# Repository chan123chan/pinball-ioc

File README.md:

# pinball-ioc
Hard and Software for our pinball machine

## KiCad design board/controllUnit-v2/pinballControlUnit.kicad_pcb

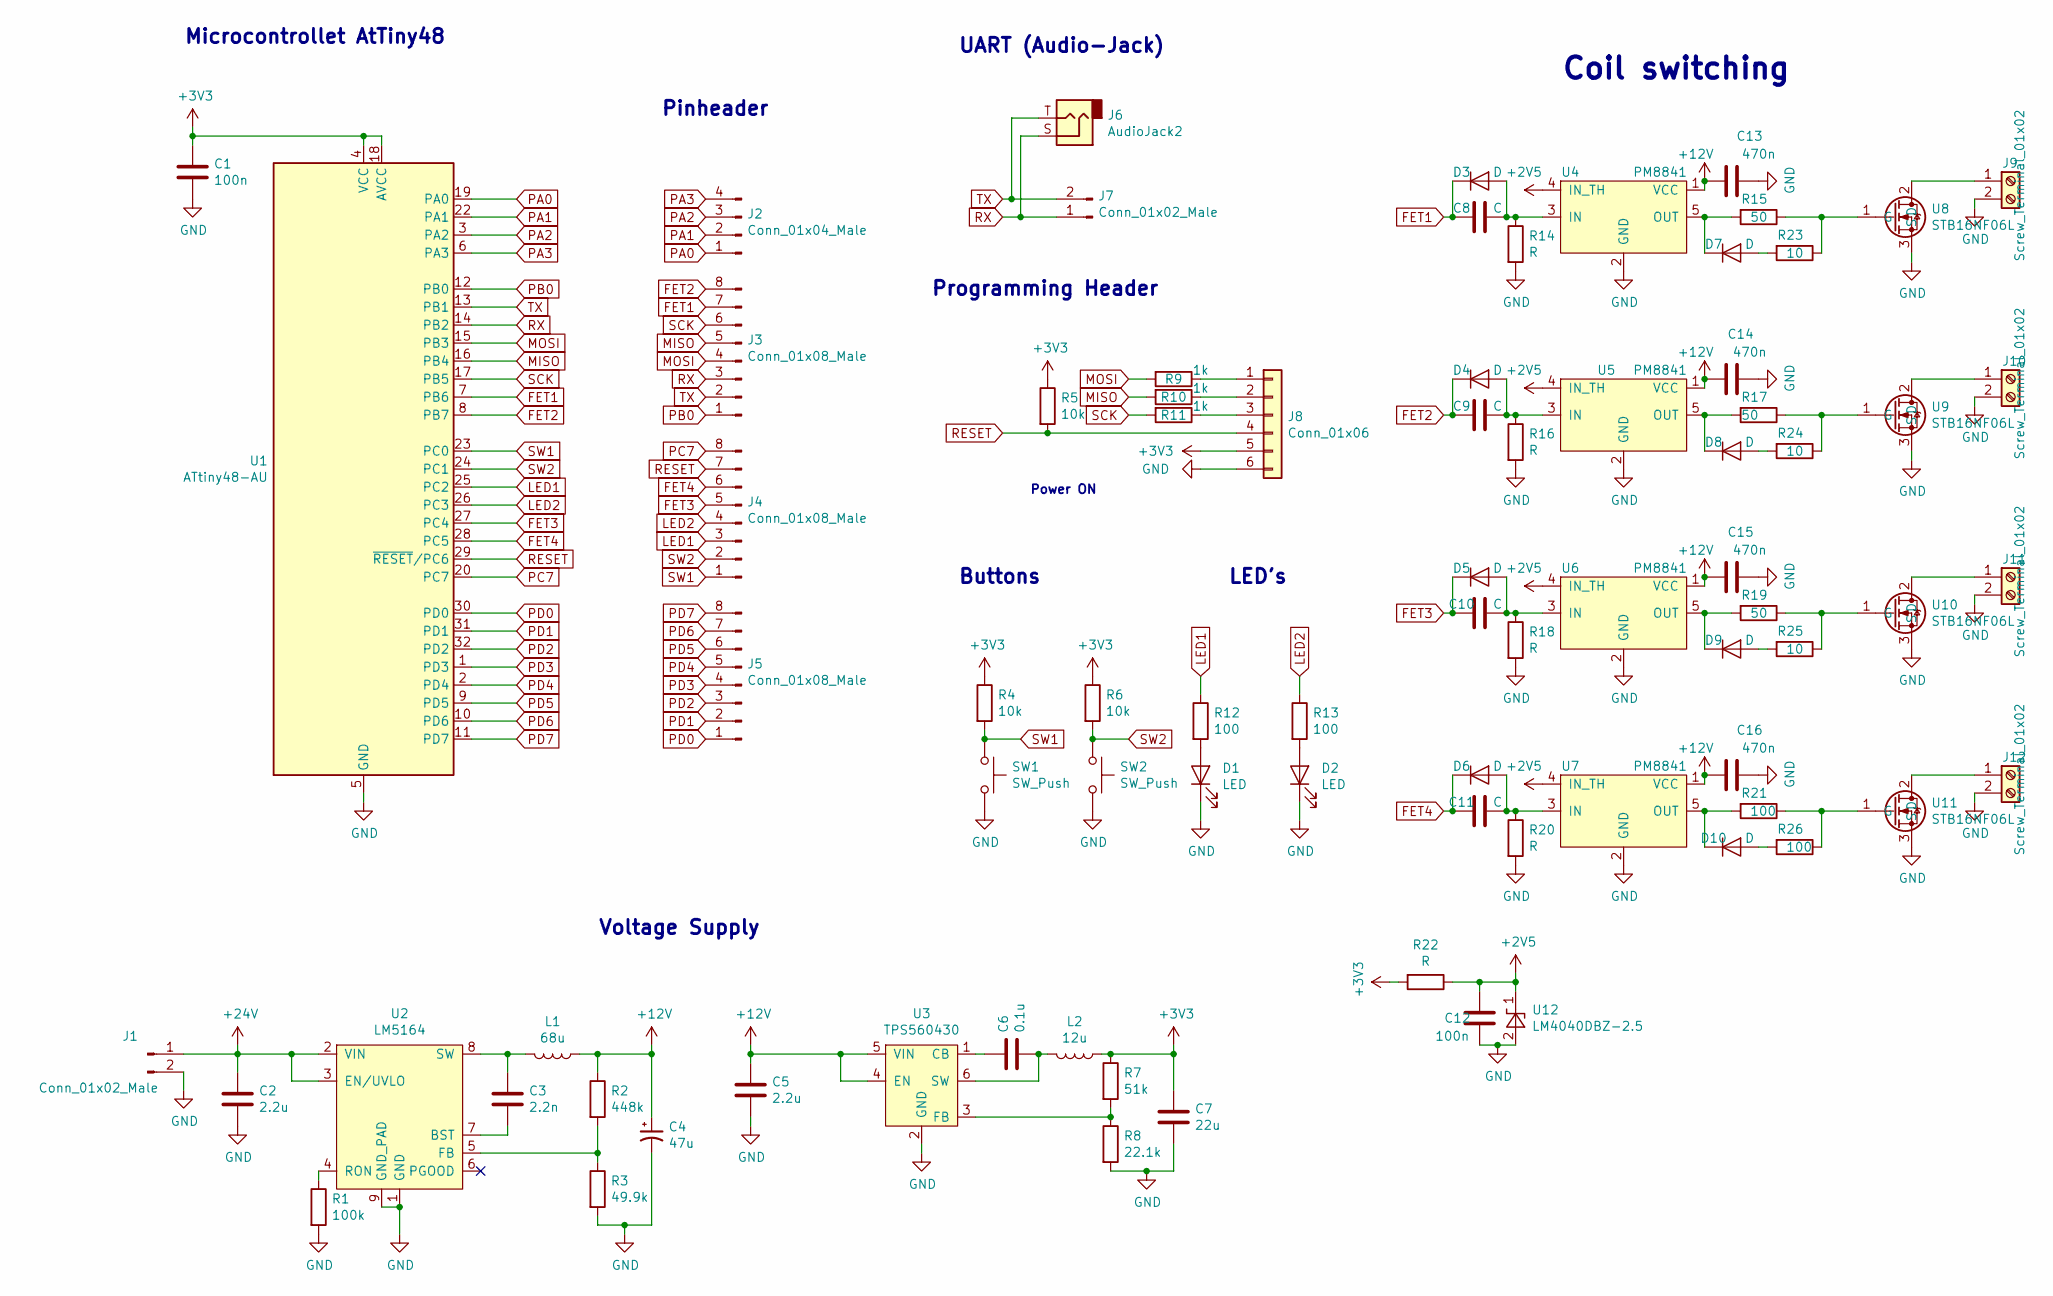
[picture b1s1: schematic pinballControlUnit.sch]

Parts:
C1, C12: 100n; C_0805_2012Metric
C2: 2.2u; C_1206_3216Metric
C3: 2.2n; C_0805_2012Metric
C4: 47u; C_Elec_6.3x5.8
C5: 2.2u; C_0805_2012Metric
C6: 0.1u; C_0805_2012Metric
C7: 22u; C_0805_2012Metric
C8, C9, C10, C11: C; C_0805_2012Metric
C13, C14, C15, C16: 470n; C_0805_2012Metric
D1, D2: LED; LED_0805_2012Metric
D3, D4, D5, D6, D7, D8, D9, D10: D; LED_0805_2012Metric
J1, J7: Conn_01x02_Male; PinHeader_1x02_P2.54mm_Vertical
J2: Conn_01x04_Male; PinHeader_1x04_P2.54mm_Vertical
J3, J4, J5: Conn_01x08_Male; PinHeader_1x08_P2.54mm_Vertical
J6: AudioJack2; Jack_3.5mm_CUI_SJ-3523-SMT_Horizontal
J8: Conn_01x06; PinHeader_1x06_P2.54mm_Vertical
J9, J10, J11, J12: Screw_Terminal_01x02; TerminalBlock_MetzConnect_Type011_RT05502HBWC_1x02_P5.00mm_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
L1: 68u; L_MSS1246-683MLB
L2: 12u; L_SDR0403-120ML
R1: 100k; R_0805_2012Metric
R2: 448k; R_0805_2012Metric
R3: 49.9k; R_0805_2012Metric
R4, R5, R6: 10k; R_0805_2012Metric
R7: 51k; R_0805_2012Metric
R8: 22.1k; R_0805_2012Metric
R9, R10, R11: 1k; R_0805_2012Metric
R12, R13, R21, R26: 100; R_0805_2012Metric
R14, R16, R18, R20, R22: R; R_0805_2012Metric
R15, R17, R19: 50; R_0805_2012Metric
R23, R24, R25: 10; R_0805_2012Metric
SW1, SW2: SW_Push; SW_SPST_B3S-1000
U1: ATtiny48-AU; TQFP-32_7x7mm_P0.8mm
U2: LM5164; TI_SO-PowerPAD-8
U3: TPS560430; SOT-23-6_Handsoldering
U4, U5, U6, U7: PM8841; SOT-23-5_HandSoldering
U8, U9, U10, U11: STB16NF06L; TO-263-2
U12: LM4040DBZ-2.5; SOT-23

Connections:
+2V5: C12.1, R22.1, U4.4 (IN_TH), U5.4 (IN_TH), U6.4 (IN_TH), U7.4 (IN_TH), U12.1 (K)
+3V3: C1.1, C7.1, J8.5, L2.1, R4.1, R5.1, R6.1, R7.1, R22.2, U1.4 (VCC), U1.18 (AVCC)
+12V: C4.1, C5.1, C13.1, C14.1, C15.1, C16.1, L1.1, R2.1, U3.4 (EN), U3.5 (VIN), U4.1 (VCC), U5.1 (VCC), U6.1 (VCC), U7.1 (VCC)
+24V: C2.1, J1.1, U2.2 (VIN), U2.3 (EN/UVLO)
FET1: C8.2, D3.1 (K), J3.7, U1.7 (PB6)
FET2: C9.2, D4.1 (K), J3.8, U1.8 (PB7)
FET3: C10.2, D5.1 (K), J4.5, U1.27 (PC4)
FET4: C11.2, D6.1 (K), J4.6, U1.28 (PC5)
GND: C1.2, C2.2, C4.2, C5.2, C7.2, C12.2, C13.2, C14.2, C15.2, C16.2, D1.1 (K), D2.1 (K), J1.2, J8.6, J9.2, J10.2, J11.2, J12.2, R1.2, R3.2, R8.2, R14.2, R16.2, R18.2, R20.2, SW1.2, SW2.2, U1.5 (GND), U1.21 (GND), U2.1 (GND), U2.9 (GND_PAD), U3.2 (GND), U4.2 (GND), U5.2 (GND), U6.2 (GND), U7.2 (GND), U8.3 (S), U9.3 (S), U10.3 (S), U11.3 (S), U12.2 (A)
LED1: J4.3, R12.1, U1.25 (PC2)
LED2: J4.4, R13.1, U1.26 (PC3)
MISO: J3.5, R10.2, U1.16 (PB4)
MOSI: J3.4, R9.2, U1.15 (PB3)
unnamed: C3.1, L1.2, U2.8 (SW)
unnamed: C3.2, U2.7 (BST)
unnamed: C6.1, U3.1 (CB)
unnamed: C6.2, L2.2, U3.6 (SW)
unnamed: C8.1, D3.2 (A), R14.1, U4.3 (IN)
unnamed: C9.1, D4.2 (A), R16.1, U5.3 (IN)
unnamed: C10.1, D5.2 (A), R18.1, U6.3 (IN)
unnamed: C11.1, D6.2 (A), R20.1, U7.3 (IN)
unnamed: D1.2 (A), R12.2
unnamed: D2.2 (A), R13.2
unnamed: D7.1 (K), R15.2, U4.5 (OUT)
unnamed: D7.2 (A), R23.2
unnamed: D8.1 (K), R17.2, U5.5 (OUT)
unnamed: D8.2 (A), R24.2
unnamed: D9.1 (K), R19.2, U6.5 (OUT)
unnamed: D9.2 (A), R25.2
unnamed: D10.1 (K), R21.2, U7.5 (OUT)
unnamed: D10.2 (A), R26.2
unnamed: J8.1, R9.1
unnamed: J8.2, R10.1
unnamed: J8.3, R11.1
unnamed: J9.1, U8.2 (D)
unnamed: J10.1, U9.2 (D)
unnamed: J11.1, U10.2 (D)
unnamed: J12.1, U11.2 (D)
unnamed: R1.1, U2.4 (RON)
unnamed: R2.2, R3.1, U2.5 (FB)
unnamed: R7.2, R8.1, U3.3 (FB)
unnamed: R15.1, R23.1, U8.1 (G)
unnamed: R17.1, R24.1, U9.1 (G)
unnamed: R19.1, R25.1, U10.1 (G)
unnamed: R21.1, R26.1, U11.1 (G)
PA0: J2.1, U1.19 (PA0)
PA1: J2.2, U1.22 (PA1)
PA2: J2.3, U1.3 (PA2)
PA3: J2.4, U1.6 (PA3)
PB0: J3.1, U1.12 (PB0)
PC7: J4.8, U1.20 (PC7)
PD0: J5.1, U1.30 (PD0)
PD1: J5.2, U1.31 (PD1)
PD2: J5.3, U1.32 (PD2)
PD3: J5.4, U1.1 (PD3)
PD4: J5.5, U1.2 (PD4)
PD5: J5.6, U1.9 (PD5)
PD6: J5.7, U1.10 (PD6)
PD7: J5.8, U1.11 (PD7)
RESET: J4.7, J8.4, R5.2, U1.29 (~RESET~/PC6)
RX: J3.3, J6.S, J7.1, U1.14 (PB2)
SCK: J3.6, R11.2, U1.17 (PB5)
SW1: J4.1, R4.2, SW1.1, U1.23 (PC0)
SW2: J4.2, R6.2, SW2.1, U1.24 (PC1)
TX: J3.2, J6.T, J7.2, U1.13 (PB1)

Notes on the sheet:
Pinheader
Microcontrollet AtTiny48
Voltage Supply
Power ON
Buttons
LED's
Programming Header
UART (Audio-Jack)
Coil switching

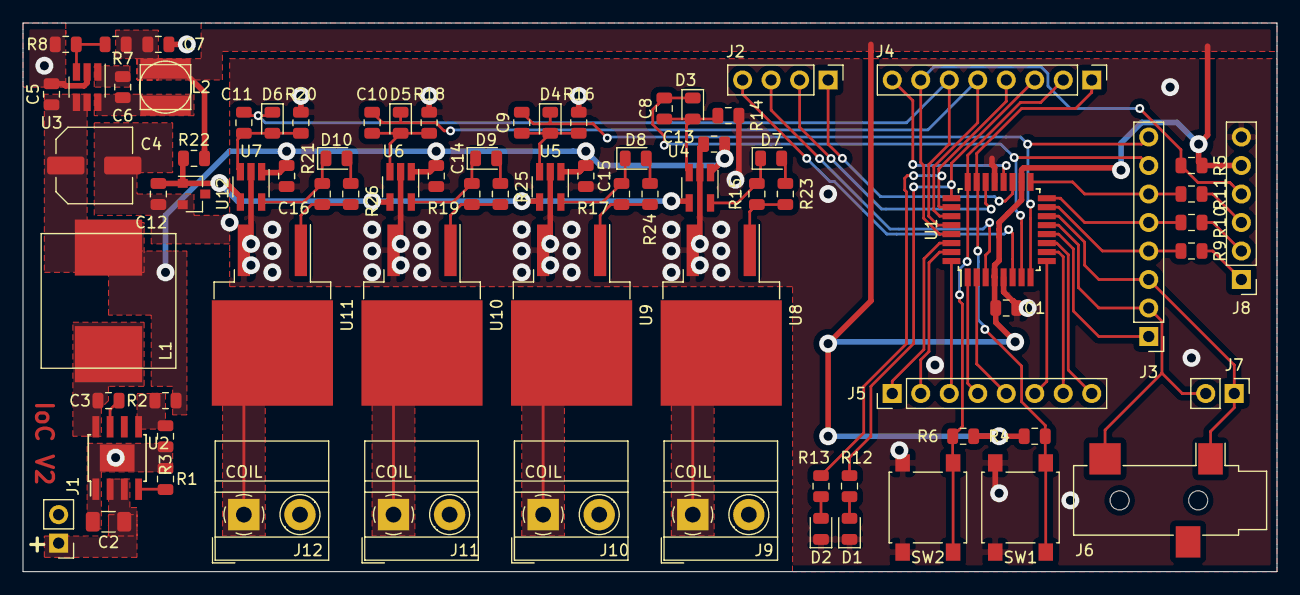
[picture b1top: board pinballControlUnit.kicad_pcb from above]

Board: 2 copper layers, 111.8 x 48.9 mm, 80 parts (0 on the bottom side), 65 nets.

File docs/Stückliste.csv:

ID;Bezeichner;Gehäuse;Stückzahl;Bezeichnung;Anbieter und Referenz
1;L2;L_0805_2012Metric_Pad1.15x1.40mm_HandSolder;1;12u;
2;R19,R21,R17,R12,R13,R15;R_0805_2012Metric;6;100;
3;U4,U6,U5,U7;SOT-23-5_HandSoldering;4;PM8841;
4;R1;R_0805_2012Metric;1;100k;
5;D1,D2;LED_0805_2012Metric;2;LED;
6;U11,U8,U9,U10;TO-263-2;4;STB16NF06L;
7;C3;C_0805_2012Metric;1;2.2n;
8;J4,J5,J3;PinHeader_1x08_P2.54mm_Vertical;3;Conn_01x08_Male;
9;SW1,SW2;SW_SPST_B3S-1000;2;SW_Push;
10;U1;TQFP-32_7x7mm_P0.8mm;1;ATtiny48-AU;
11;J7,J1;PinHeader_1x02_P2.54mm_Vertical;2;Conn_01x02_Male;
12;J8;PinHeader_1x06_P2.54mm_Vertical;1;Conn_01x06;
13;R9,R10,R11;R_0805_2012Metric;3;1k;
14;R5,R6,R4;R_0805_2012Metric;3;10k;
15;R3;R_0805_2012Metric;1;49.9k;
16;R2;R_0805_2012Metric;1;448k;
17;R8;R_0805_2012Metric;1;22.1k;
18;R7;R_0805_2012Metric;1;51k;
19;J6;Jack_3.5mm_CUI_SJ-3523-SMT_Horizontal;1;AudioJack2;
20;C1;C_0805_2012Metric;1;100n;
21;J9,J10,J11,J12;TerminalBlock_MetzConnect_Type011_RT05502HBWC_1x02_P5.00mm_Horizontal;4;Screw_Terminal_01x02;
22;J2;PinHeader_1x04_P2.54mm_Vertical;1;Conn_01x04_Male;
23;C2,C5;C_0805_2012Metric;2;2.2u;
24;C4;CP_Elec_6.3x3.9;1;47u;
25;C6;C_0805_2012Metric;1;0.1u;
26;C7;C_0805_2012Metric;1;22u;
27;L1;L_0805_2012Metric_Pad1.15x1.40mm_HandSolder;1;68u;
28;U2;TI_SO-PowerPAD-8;1;LM5164;
29;U3;SOT-23-6_Handsoldering;1;TPS560430;

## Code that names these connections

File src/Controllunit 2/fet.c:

#include <avr/io.h>
#include <stdio.h>
#include <stddef.h>
#include "fet.h"

#define FET1_BIT PB6
#define FET1_PORT PORTB
#define FET1_DIR DDRB

#define FET2_BIT PB7
#define FET2_PORT PORTB
#define FET2_DIR DDRB

#define FET3_BIT PC4
#define FET3_PORT PORTC
#define FET3_DIR DDRC

#define FET4_BIT PC5
#define FET4_PORT PORTC
#define FET4_DIR DDRC

void initFet(void){
  // Pull up ausgeschalten
  BIT_SET(&MCUCR, PUD);
  BIT_CLEAR(&FET1_PORT, FET1_BIT);
  BIT_CLEAR(&FET2_PORT, FET2_BIT);
  BIT_CLEAR(&FET3_PORT, FET3_BIT);
  BIT_CLEAR(&FET4_PORT, FET4_BIT);

  BIT_SET(&FET1_DIR, FET1_BIT);
  BIT_SET(&FET2_DIR, FET2_BIT);
  BIT_SET(&FET3_DIR, FET3_BIT);
  BIT_SET(&FET4_DIR, FET4_BIT);

  // alle FET's werden ausgeschalten
};

void fetOn(uint8_t nbr){
  switch(nbr){
    case 1:
      BIT_CLEAR(&FET1_DIR, FET1_BIT);
    break;
    case 2:
      BIT_CLEAR(&FET2_DIR, FET2_BIT);
    break;
    case 3:
      BIT_CLEAR(&FET3_DIR, FET3_BIT);
    break;
    case 4:
      BIT_CLEAR(&FET4_DIR, FET4_BIT);
    break;
  }
}
void fetOff(uint8_t nbr){
  switch(nbr){
    case 1:
      BIT_SET(&FET1_DIR, FET1_BIT);
    break;
    case 2:
      BIT_SET(&FET2_DIR, FET2_BIT);
    break;
    case 3:
      BIT_SET(&FET3_DIR, FET3_BIT);
    break;
    case 4:
      BIT_SET(&FET4_DIR, FET4_BIT);
    break;
  }
}

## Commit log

2019-09-08 Schema controllUnit verbessert
2019-09-13 V2 fertig
2019-09-14 Silk screen angepasst und fab layer
2019-09-19 hier sourcecode
2019-09-22 Spannungsversorgung und FETS komplett geändert
2019-09-22 doku hinzugefügt
2019-09-22 Delete Icon
    kei anig was das gsi esch
2019-09-22 .lib files werden nicht mehr ignoriert
2019-09-22 Projekt Library hinzugefügt
    Projekt aufgeräumt
2019-09-22 Update .gitignore
    Mac .DS_Store werden ignoriert
2019-09-22 Schema aktualisiert
2019-09-22 Schema fertig und David geschickt
2019-09-23 Leiterplatte gelayoutet
2019-09-24 Schaltregler Layout gemäss Datenblatt angepasst
    TPS560430
    LM5164
2019-09-25 Schema+Layout fertig
    Stückliste erstellt
2019-09-25 Leiterplatte soweit fertig
2019-09-26 Gerber files erstellt
2019-09-27 Update pinballControlUnit.kicad_pcb
    Änderungen Simon Burkhardt
